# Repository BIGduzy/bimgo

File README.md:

# BIMGO
------
## Usage
### Front-end
Use `npm start` to start the front-end development server which is automatically reloaded when you edit the Javascript.
Use `npm run build` to build the front-end JavaScript to bundle.js which is used for production.

## TODO:
### Front-end
- Use the API;
- Minify/uglify the production code

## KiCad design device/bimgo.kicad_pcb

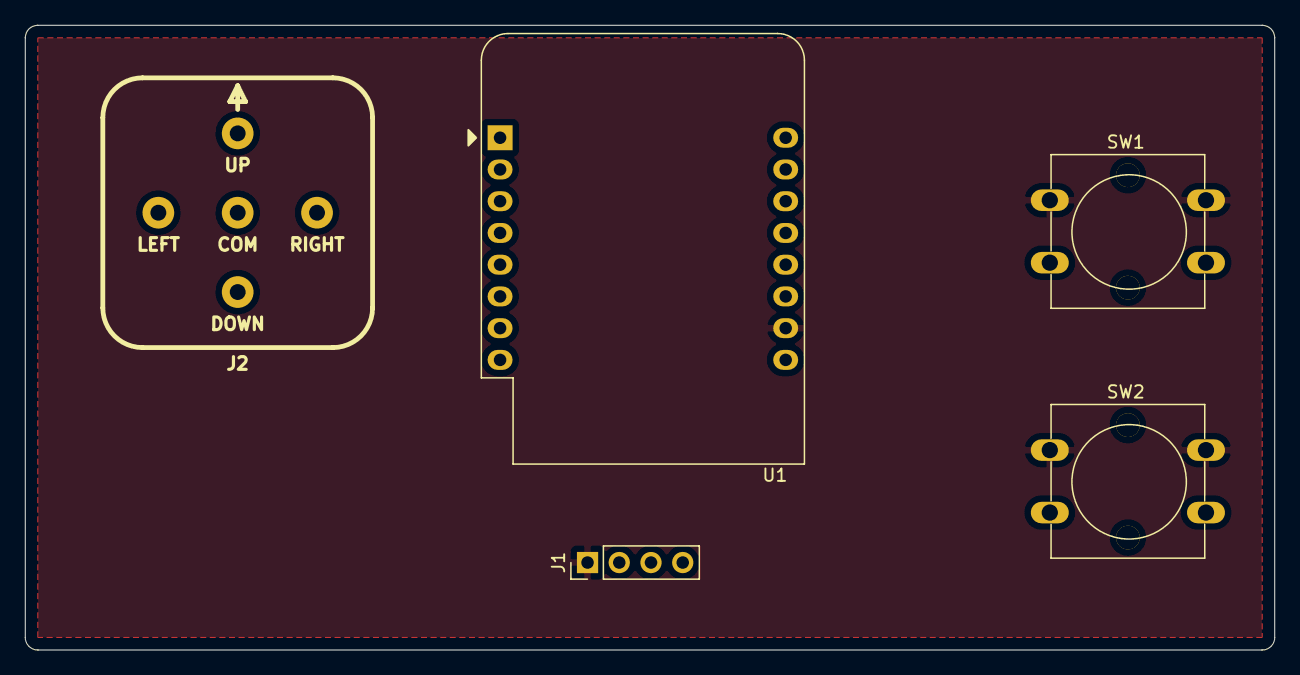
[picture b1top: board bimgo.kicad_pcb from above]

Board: 2 copper layers, 100.0 x 50.0 mm, 5 parts (0 on the bottom side), 11 nets, no tracks yet.

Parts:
J1: Conn_01x04_Female; PinHeader_1x04_P2.54mm_Vertical
J2: JOYSTICK
SW1, SW2: SW_Push; SW_PUSH-12mm_with_poles
U1: WeMos_D1_mini; WEMOS_D1_mini_light

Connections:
+3V3: J1.2, U1.8
GND: J1.1, SW1.1, SW2.1, U1.10
unnamed: J1.3, U1.14
unnamed: J1.4, U1.13
unnamed: J2.COM, U1.3
unnamed: J2.D, U1.12
unnamed: J2.L, U1.5
unnamed: J2.R, U1.4
unnamed: J2.U, U1.11
unnamed: SW1.2, U1.6
unnamed: SW2.2, U1.7

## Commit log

2018-02-13 Implemented the front-end
2018-02-13 README styling
2018-02-14 It's wednesday my dudes
2018-02-15 Create LICENSE
    A license file was desperately needed.
2018-02-23 Connected front-end with API
2018-06-08 Fixed css :bug: where text was not aligned
2019-02-08 Fixed some eslint errors
2019-03-29 Basic react setup
2019-03-31 Implemented static version of the side using react
2019-03-31 Fixed the eslint
2019-03-31 Decorator fix for eslint
2019-03-31 Added basic redux implementation and solved code standard issues
2019-03-31 Added prop-types to dependencies
2019-03-31 Implemented better ducks
2019-03-31 Implemented API connection
2019-03-31 Moved front-end to its own folder and removed some old files
2019-04-01 Fixed some casing issues
2019-04-01 Fixed blocked by CORS :bug:
2019-04-01 Implemented react-router with a placeholder rooms page
2019-04-05 Added simple socket functionality
2019-04-05 Fixed "Cannot GET" after refresh :bug:
2019-04-15 Added Kicad
